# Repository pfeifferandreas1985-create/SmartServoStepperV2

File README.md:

# 🦾 SmartServoStepperV2

A high-performance Smart Stepper Servo based on the ESP32-C3 Super Mini, TMC2209 driver, and AS5600 magnetic encoder.

## 🚀 Key Features (v3.0.0 Stable)
- **Direct Frequency Positioning:** Oscillation-free, ultra-precise CNC-style open-loop positioning via `FastAccelStepper`.
- **Dual Communication:** Hybrid WiFi (FritzBox Station Mode + Fallback Access Point).
- **Web Dashboard:** Interactive HTML/JS GUI with real-time telemetry (RPS, Angle).
- **Hybrid TMC2209 Control:** Hardware timers for perfect Step/Dir movement, paired with UART for smart driver configuration (SpreadCycle, current limits).

## 📌 Hardware Configuration
| Component | ESP32-C3 GPIO | Function |
| :--- | :--- | :--- |
| UART RX | 5 | Data from TMC2209 |
| UART TX | 6 | Data to TMC2209 |
| ENABLE | 3 | Driver Stage Control |
| STEP | 4 | Hardware Timer Steps |
| DIR | 2 | Hardware Timer Direction |
| I2C SDA | 0 | AS5600 Data |
| I2C SCL | 10 | AS5600 Clock |
| Status LED| 8 | System Heartbeat |

## 📦 Software Setup
1. **Arduino IDE Settings:**
   - Board: `ESP32C3 Dev Module`
   - USB CDC On Boot: **ENABLED** (Required for Serial Monitor)
   - Flash Mode: **DIO**
2. **Libraries Required:**
   - `TMCStepper`
   - `FastAccelStepper`
   - `ArduinoJson (v7)`
   - `WebSocketsServer`
   - `AS5600`
3. **Usage:**
   - Upload `SmartServoStepperV2.ino`.
   - Access the dashboard at `192.168.178.78` (FritzBox) or `192.168.4.1` (AP).

## 🛠 Stability Fixes
- **Startup Delay:** A 3-second delay in `setup()` ensures the USB-CDC port enumerates correctly.
- **Pin Mapping:** Re-routed signals away from sensitive strap pins (GPIO 9) to ensure reliable boots.
- **Encoder Filtering:** 20ms RPS window to prevent aliasing at high speeds.

---
*Maintained by pfeifferandreas1985*

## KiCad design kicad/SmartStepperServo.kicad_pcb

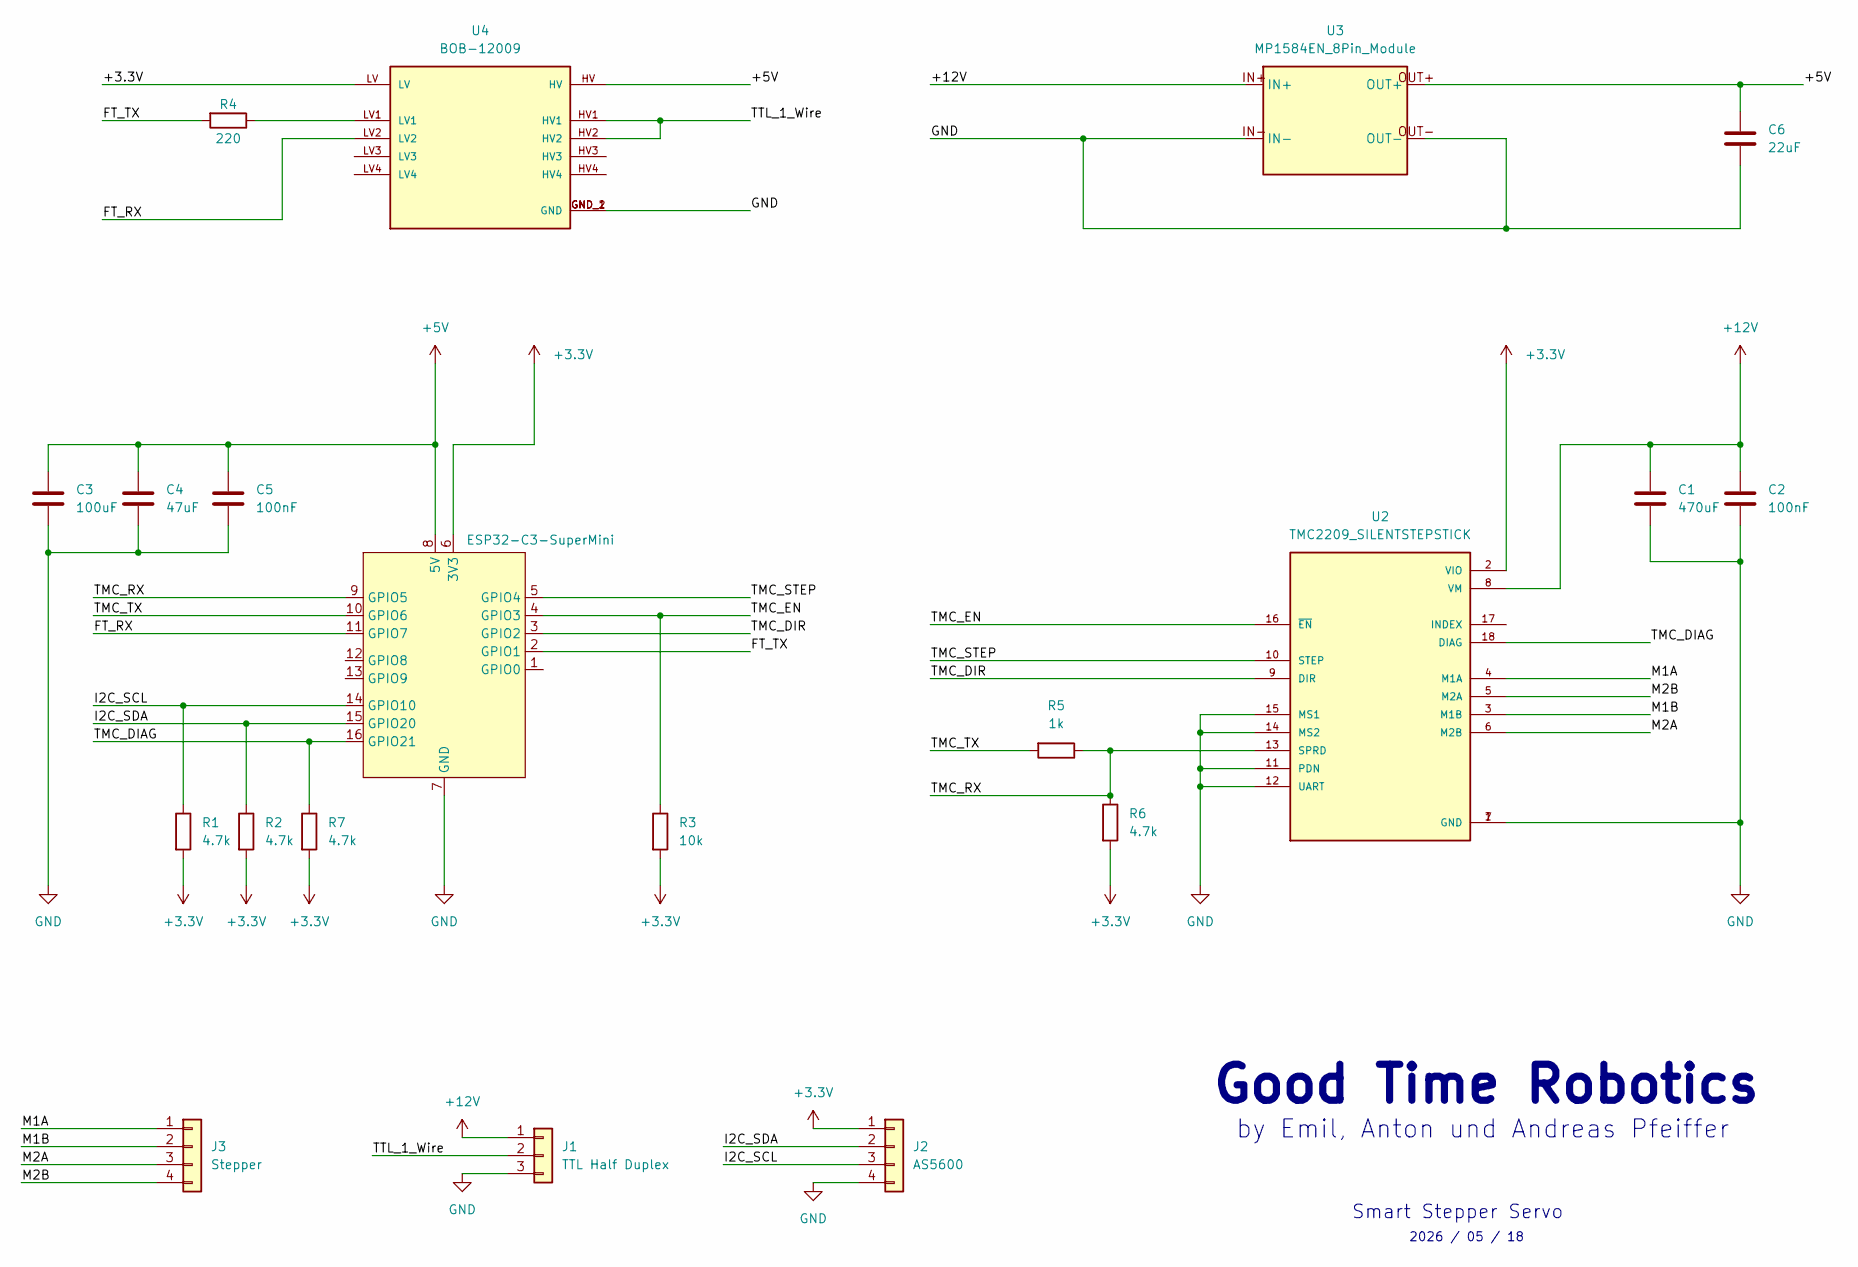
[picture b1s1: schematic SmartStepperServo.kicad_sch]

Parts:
C1: 470uF; CP_Radial_D6.3mm_P2.50mm
C2, C5: 100nF; C_Disc_D3.8mm_W2.6mm_P2.50mm
C3: 100uF; CP_Radial_D6.3mm_P2.50mm
C4: 47uF; CP_Radial_D6.3mm_P2.50mm
C6: 22uF; C_Disc_D3.8mm_W2.6mm_P2.50mm
J1: TTL Half Duplex; JST_XH_B3B-XH-A_1x03_P2.50mm_Vertical
J2: AS5600; JST_XH_B4B-XH-A_1x04_P2.50mm_Vertical
J3: Stepper; JST_XH_B4B-XH-A_1x04_P2.50mm_Vertical
R1, R2, R6, R7: 4.7k; R_Axial_DIN0207_L6.3mm_D2.5mm_P7.62mm_Horizontal
R3: 10k; R_Axial_DIN0207_L6.3mm_D2.5mm_P7.62mm_Horizontal
R4: 220; R_Axial_DIN0207_L6.3mm_D2.5mm_P7.62mm_Horizontal
R5: 1k; R_Axial_DIN0207_L6.3mm_D2.5mm_P7.62mm_Horizontal
U1: ESP32-C3-SuperMini
U2: TMC2209_SILENTSTEPSTICK; MODULE_TMC2209_SILENTSTEPSTICK; PARTREV 1.20
U3: MP1584EN_8Pin_Module
U4: BOB-12009; CONV_BOB-12009; PARTREV 01

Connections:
+3.3V: J2.1, R1.2, R2.2, R3.2, R6.2, R7.2, U1.6 (3V3), U2.2 (VIO), U4.LV
+5V: C3.2, C4.2, C5.2, C6.1, U1.8 (5V), U3.OUT+, U4.HV
+12V: C1.1, C2.1, J1.1, U2.8 (VM), U3.IN+
/FT_RX: U1.11 (GPIO7), U4.LV2
/FT_TX: R4.2, U1.2 (GPIO1)
/I2C_SCL: J2.3, R1.1, U1.14 (GPIO10)
/I2C_SDA: J2.2, R2.1, U1.15 (GPIO20)
/M1A: J3.1, U2.4 (M1A)
/M1B: J3.2, U2.3 (M1B)
/M2A: J3.3, U2.6 (M2B)
/M2B: J3.4, U2.5 (M2A)
/TMC_DIAG: R7.1, U1.16 (GPIO21), U2.18 (DIAG)
/TMC_DIR: U1.3 (GPIO2), U2.9 (DIR)
/TMC_EN: R3.1, U1.4 (GPIO3), U2.16 (~EN)
/TMC_RX: R5.1, R6.1, U1.9 (GPIO5), U2.13 (SPRD)
/TMC_STEP: U1.5 (GPIO4), U2.10 (STEP)
/TMC_TX: R5.2, U1.10 (GPIO6)
/TTL_1_Wire: J1.2, U4.HV1, U4.HV2
GND: C1.2, C2.2, C3.1, C4.1, C5.1, C6.2, J1.3, J2.4, U1.7 (GND), U2.1 (GND), U2.7 (GND), U2.11 (PDN), U2.12 (UART), U2.14 (MS2), U2.15 (MS1), U3.IN-, U3.OUT-, U4.GND_1 (GND), U4.GND_2 (GND)
unnamed: R4.1, U4.LV1

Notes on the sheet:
Good Time Robotics
2026 / 05 / 18
Smart Stepper Servo
by Emil, Anton und Andreas Pfeiffer

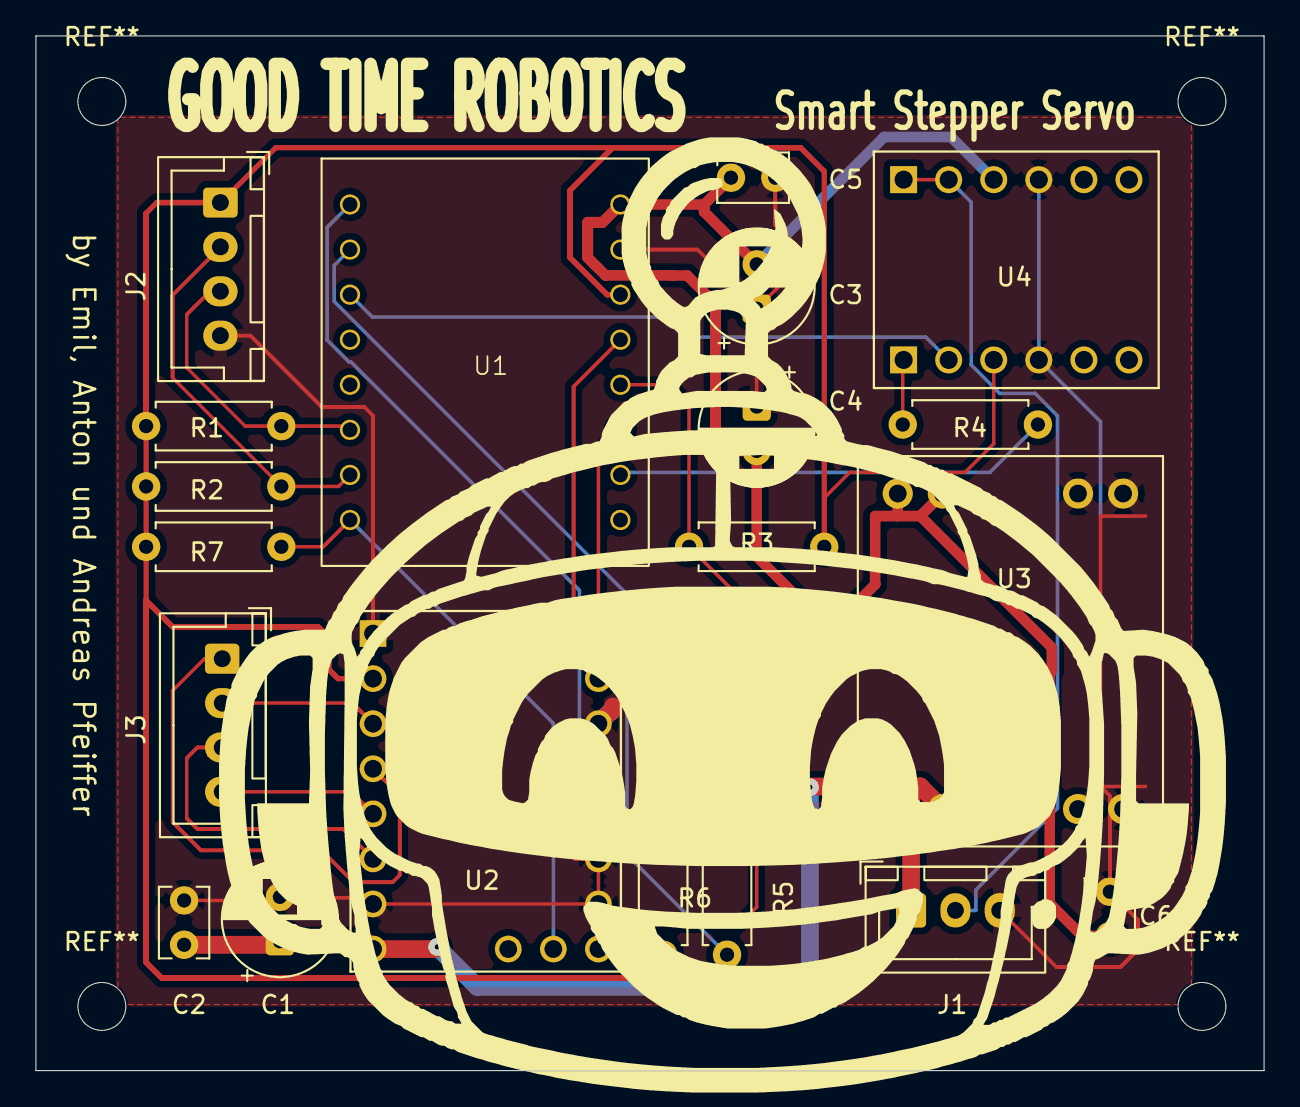
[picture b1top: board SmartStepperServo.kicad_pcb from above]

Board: 2 copper layers, 69.2 x 58.3 mm, 20 parts (0 on the bottom side), 20 nets.

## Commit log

2026-05-12 Initial commit: V2 Hardware Documentation with ESP32-C3 and TMC2209
2026-05-12 Added ESP32-C3 Firmware and KiCad project structure
2026-05-12 Updated README with software and hardware instructions
2026-05-12 Added premium HTML version of the PCB wiring schematic
2026-05-15 FIX: Established stable TMC2209 UART communication on GPIO 5/6
2026-05-15 DOCS: Updated master schematic to v2.0 Verified with final protection circuit details
2026-05-16 Final stable release v2.9.2 - Complete hardware fix, PID position control, and dashboard integration
2026-05-16 Refactor: Switch to pure Direct Frequency (CNC) control via FastAccelStepper. Removed PID loops to eliminate oscillations, implementing optimal hardware timer stepping.
2026-05-16 Docs: Update README.md to v3.0.0 reflecting the new FastAccelStepper Direct Frequency architecture and updated PIN configurations
2026-05-17 docs: Update PCB wiring schematic to perfectly match .ino firmware pinout (STEP=4, DIR=2, SCL=10, Feetech Level Shifter)
2026-05-17 feat: Add KiCad schematic reference doc + fix swapped UART comments in config.h (1k on TX/GPIO6)
2026-05-17 docs: Add HTML version of KiCad schematic reference
2026-05-17 docs: Add module-to-module wiring guide with point-to-point netlist (HTML)
2026-05-17 docs: Add Master-Schaltplan v2.2 with Dupont connectors J1/J2 and module-based layout
2026-05-17 docs: Add high-resolution KiCad schematic diagrams to Master-Schaltplan and HTML docs
2026-05-17 feat: Add manufacturing cost calculation (MD & premium HTML with interactive slider)
2026-05-17 style: Update dashboard title to Good Time Robotics by Emil, Anton und Andreas Pfeiffer
2026-05-17 style: Center and enlarge dashboard header brand text, restore technical description
2026-05-17 style: Restore Smart Servo Stepper to centered dashboard header title
2026-05-17 style: Keep SmartServo Stepper title on the left and place brand title centered in the middle
2026-05-17 style: Split brand header centered text into large title and smaller author line
2026-05-18 Update hardware schematics, PCB layout, PDF exports, and review reports for V2
2026-05-18 docs: Add IPC-2152 trace width calculations and KiCad Net Classes to master plan
2026-05-19 Add gerber files, manufacturing zip and KiCad board/schematic source files
